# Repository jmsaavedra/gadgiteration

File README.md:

gadgiteration
=============

Hardware and firmware for the gadgiteration noisemaker v2.0

http://gadgiteration.org

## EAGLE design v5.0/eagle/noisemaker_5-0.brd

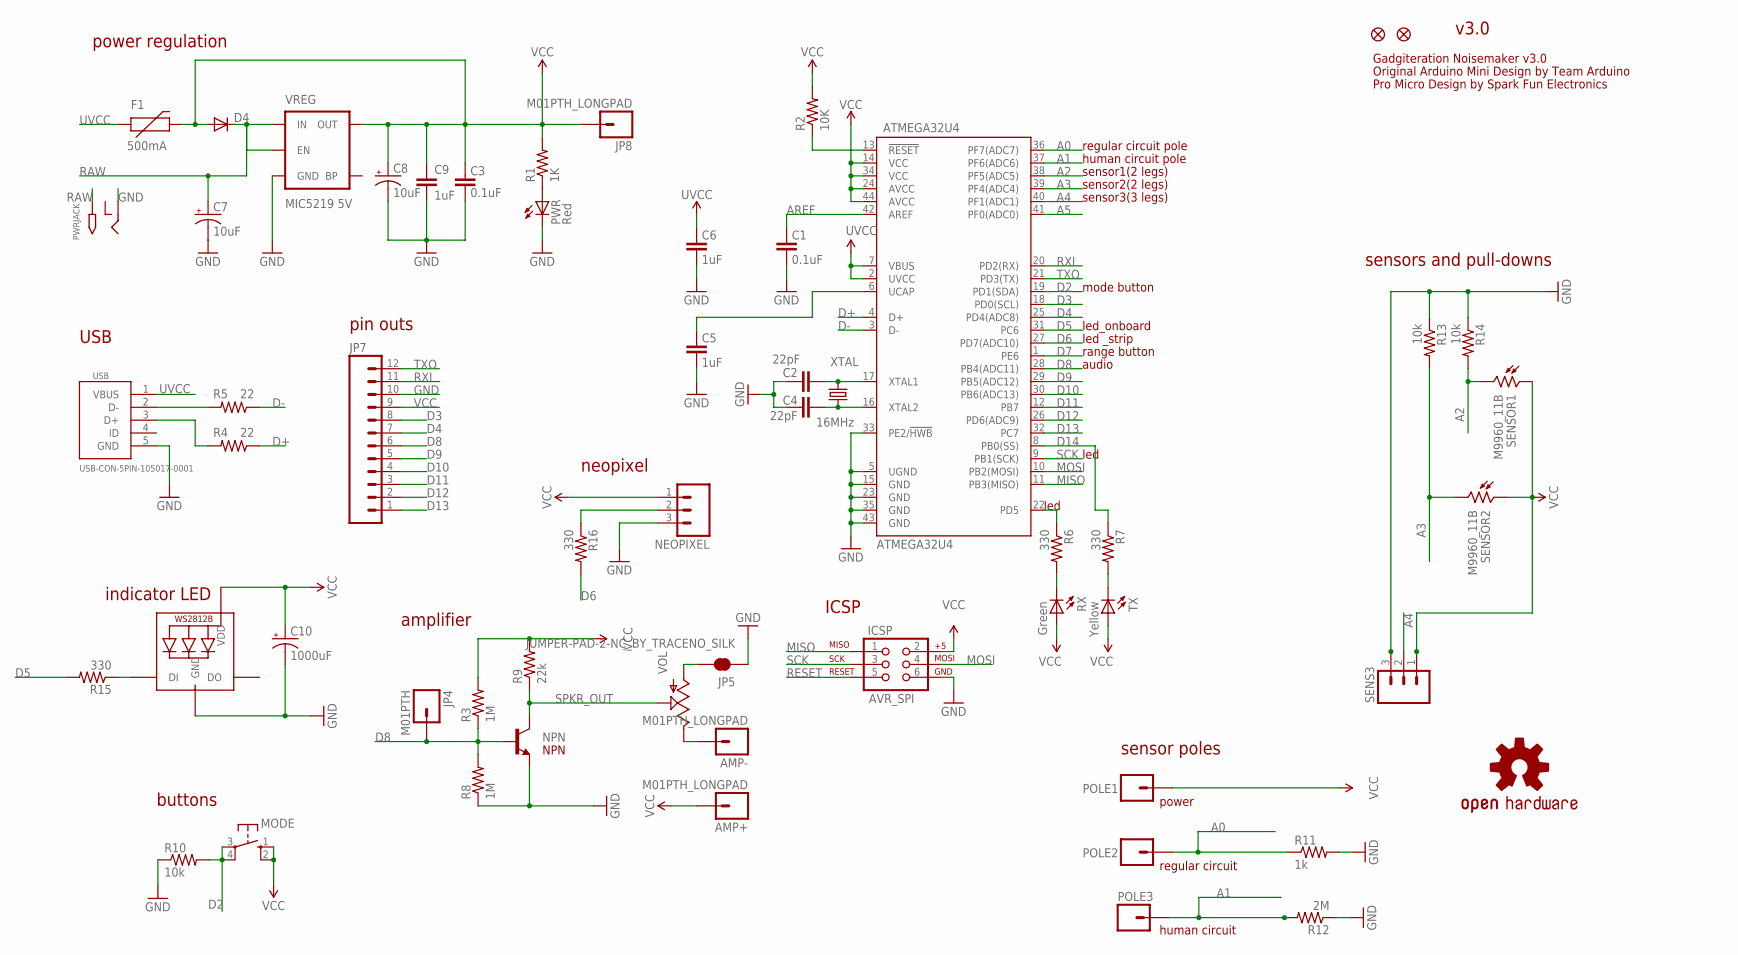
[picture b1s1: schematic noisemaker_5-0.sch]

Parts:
AMP+: M01PTH_LONGPAD; 1X01_LONGPAD
AMP-: M01PTH_LONGPAD; 1X01_LONGPAD
ATMEGA32U4: ATMEGA32U4; SPARKFUN-DIGITALIC_TQFP44
C1, C3: 0.1uF; 1206
C2, C4: 22pF; 0603-CAP
C5, C6, C9: 1uF; 1206
C7, C8: 10uF; EIA3528-KIT
C10: 1000uF; EIA3528-KIT
D4: DIODESOD; SOD-323
F1: 500mA; PTC-1206
ICSP: AVR_SPI; 2X3
JP1, JP2: FIDUCIALUFIDUCIAL; MICRO-FIDUCIAL
JP4: M01PTH; 1X01
JP5: JUMPER-PAD-2-NC_BY_TRACENO_SILK; PAD-JUMPER-2-NC_BY_TRACE_NO_SILK
JP7: M12PTH; 1X12
JP8: M01PTH_LONGPAD; 1X01_LONGPAD
LED1: WS2812B3535; LED3535
LOGO1: OSHW-LOGOM; OSHW-LOGO-M
MODE: 10-XX; B3F-10XX
NEOPIXEL: M03LONGPADS; 1X03_LONGPADS
NPN: TRANSISTOR_NPNSOT23-3; SOT23-3
POLE1, POLE2: M01ALLIGATOR-3MM; 1X01_ALLIGATOR_3MM
POLE3: M01PTH_LONGPAD; 1X01_LONGPAD
PWR: Red; CHIPLED_1206
PWRJACK: 2.1MMJACKTHM; PJ-102A
R1: 1K; 1206
R2: 10K; 1206
R3, R8: 1M; 1206
R4, R5: 22; 1206
R6, R7, R15, R16: 330; 1206
R9: 22k; 1206
R10, R13, R14: 10k; 1206
R11: 1k; 1206
R12: 2M; 1206
RX: Green; CHIPLED_1206
SENS3: M03POGO_PIN_HOLES_ONLY; 1X03_PP_HOLES_ONLY
SENSOR1, SENSOR2: M9960_11B; M9960
TX: Yellow; CHIPLED_1206
USB: USB-CON-5PIN-105017-0001; USB-MICRO-MOLEX-105017-0001
VOL: POT; ALPS_POT
VREG: MIC5219 5V; SOT23-5
XTAL: 16MHz; CRYSTAL-SMD-5X3

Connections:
A0: ATMEGA32U4.36 (PF7(ADC7)), POLE2.1@0, POLE2.1@2, R11.1
A1: ATMEGA32U4.37 (PF6(ADC6)), POLE3.1, R12.2
A2: ATMEGA32U4.38 (PF5(ADC5)), R14.2, SENSOR1.2
A3: ATMEGA32U4.39 (PF4(ADC4)), R13.2, SENSOR2.2
A4: ATMEGA32U4.40 (PF1(ADC1)), SENS3.2
A5: ATMEGA32U4.41 (PF0(ADC0))
AREF: ATMEGA32U4.42 (AREF), C1.2
D2: ATMEGA32U4.19 (PD1(SDA)), MODE.3, MODE.4 (P1), R10.2
D3: ATMEGA32U4.18 (PD0(SCL)), JP7.8
D4: ATMEGA32U4.25 (PD4(ADC8)), JP7.7
D5: ATMEGA32U4.31 (PC6), R15.2
D6: ATMEGA32U4.27 (PD7(ADC10)), R16.2
D7: ATMEGA32U4.1 (PE6)
D8: ATMEGA32U4.28 (PB4(ADC11)), JP4.1, JP7.6, NPN.1 (B), R3.1, R8.2
D9: ATMEGA32U4.29 (PB5(ADC12)), JP7.5
D10: ATMEGA32U4.30 (PB6(ADC13)), JP7.4
D11: ATMEGA32U4.12 (PB7), JP7.3
D12: ATMEGA32U4.26 (PD6(ADC9)), JP7.2
D13: ATMEGA32U4.32 (PC7), JP7.1
D14: ATMEGA32U4.8 (PB0(SS)), R7.1
D+: ATMEGA32U4.4 (D+), R4.1
D-: ATMEGA32U4.3 (D-), R5.1
GND: ATMEGA32U4.5 (UGND), ATMEGA32U4.15 (GND), ATMEGA32U4.23 (GND), ATMEGA32U4.33 (PE2/!HWB), ATMEGA32U4.35 (GND), ATMEGA32U4.43 (GND), C1.1, C2.2, C3.1, C4.2, C5.1, C6.1, C7.C (-), C8.C (-), C9.2, C10.C (-), ICSP.6, JP5.1, JP7.10, LED1.4 (GND), NEOPIXEL.3, NPN.2 (E), PWR.C, PWRJACK.RING, R8.1, R10.1, R11.2, R12.1, R13.1, R14.1, SENS3.3, USB.5 (GND), VREG.2 (GND)
MISO: ATMEGA32U4.11 (PB3(MISO)), ICSP.1
MOSI: ATMEGA32U4.10 (PB2(MOSI)), ICSP.4
unnamed: ATMEGA32U4.16 (XTAL2), C4.1, XTAL.1
unnamed: ATMEGA32U4.17 (XTAL1), C2.1, XTAL.3 (2)
unnamed: AMP-.1, VOL.P$1 (E)
unnamed: ATMEGA32U4.6 (UCAP), C5.2
unnamed: R7.2, TX.C
unnamed: JP5.2, VOL.P$3 (A)
unnamed: R6.2, RX.C
unnamed: LED1.1 (DI), R15.1
unnamed: NEOPIXEL.2, R16.1
unnamed: PWR.A, R1.1
unnamed: R4.2, USB.3 (D+)
unnamed: R5.2, USB.2 (D-)
RAW: C7.A (+), D4.1 (C), PWRJACK.TIP, VREG.1 (IN), VREG.3 (EN)
RESET: ATMEGA32U4.13 (!RESET), ICSP.5, R2.1
RXI: ATMEGA32U4.20 (PD2(RX)), JP7.11
SCK: ATMEGA32U4.9 (PB1(SCK)), ICSP.3
SPKR_OUT: NPN.3 (C), R9.1, VOL.P$2 (S)
TXLED: ATMEGA32U4.22 (PD5), R6.1
TXO: ATMEGA32U4.21 (PD3(TX)), JP7.12
UVCC: ATMEGA32U4.2 (UVCC), ATMEGA32U4.7 (VBUS), C6.2, F1.1, USB.1 (VBUS)
VCC: AMP+.1, ATMEGA32U4.14 (VCC), ATMEGA32U4.24 (AVCC), ATMEGA32U4.34 (VCC), ATMEGA32U4.44 (AVCC), C3.2, C8.A (+), C9.1, C10.A (+), D4.2 (A), F1.2, ICSP.2, JP7.9, JP8.1, LED1.2 (VDD), MODE.1 (S), MODE.2 (S1), NEOPIXEL.1, POLE1.1@0, POLE1.1@2, R1.2, R2.2, R3.2, R9.2, RX.A, SENS3.1, SENSOR1.1, SENSOR2.1, TX.A, VREG.5 (OUT)

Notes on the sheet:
Original Arduino Mini Design by Team Arduino
Pro Micro Design by Spark Fun Electronics
v3.0
power regulation
pin outs
USB
NPN
amplifier
sensors and pull-downs
ICSP
buttons
sensor poles
human circuit
regular circuit
power
Gadgiteration Noisemaker v3.0
sensor3(3 legs)
sensor1(2 legs)
sensor2(2 legs)
human circuit pole
regular circuit pole
mode button
range button
audio
led_onboard
led
led _strip
neopixel
indicator LED

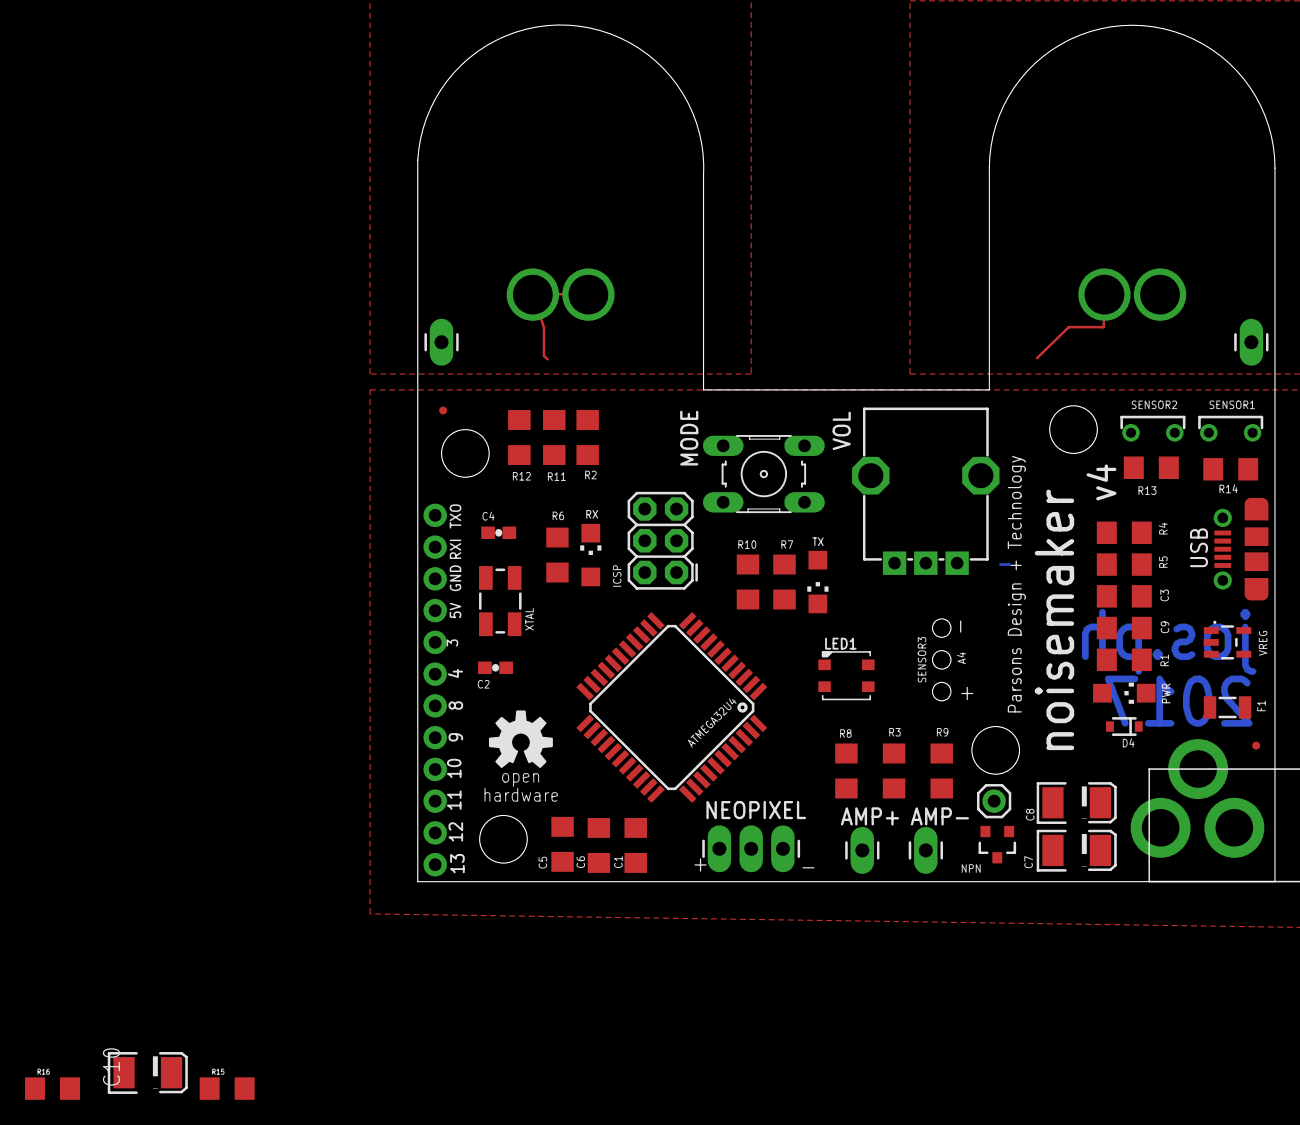
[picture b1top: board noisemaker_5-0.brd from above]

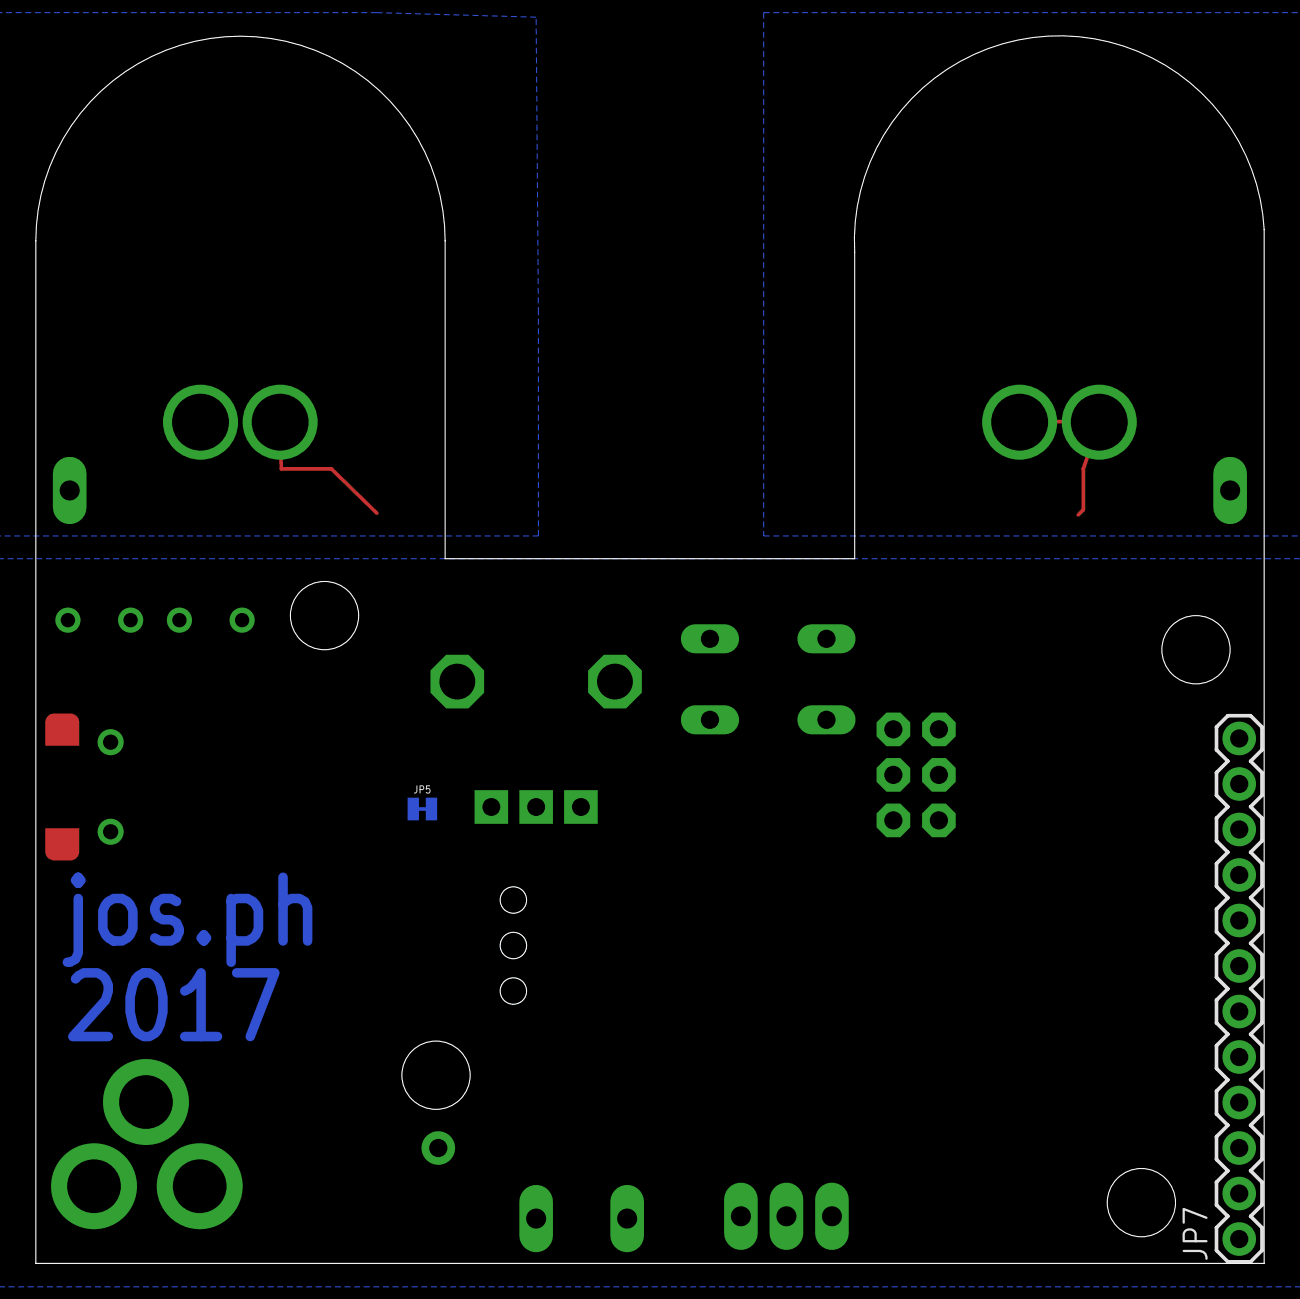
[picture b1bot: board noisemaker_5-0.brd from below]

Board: 2 copper layers, 68.6 x 68.5 mm, 57 parts (2 on the bottom side), 44 nets.

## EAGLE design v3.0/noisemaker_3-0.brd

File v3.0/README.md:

gadgIteration hardware v3.0
=============

ATmega32u4 Implementation of the Noisemaker!

###digital pinouts###

* D2 - Mode Button
* D5 - on-board LEDs. HIGH/LOW to flip LED1/LED2
* D6 - Neopixel Connection
* D7 - Range Button
* D8 - Audio out. NPN amplifier to speaker.

###analog pinouts###

* A0 - Standard Alligator In
* A1 - Human Circuit In
* A2 - SENSOR 1. 10k pull-down.
* A3 - SENSOR 2. 10k pull-down.
* A4 - SENSOR 3. VCC - SENS - GND.

###known bugs###

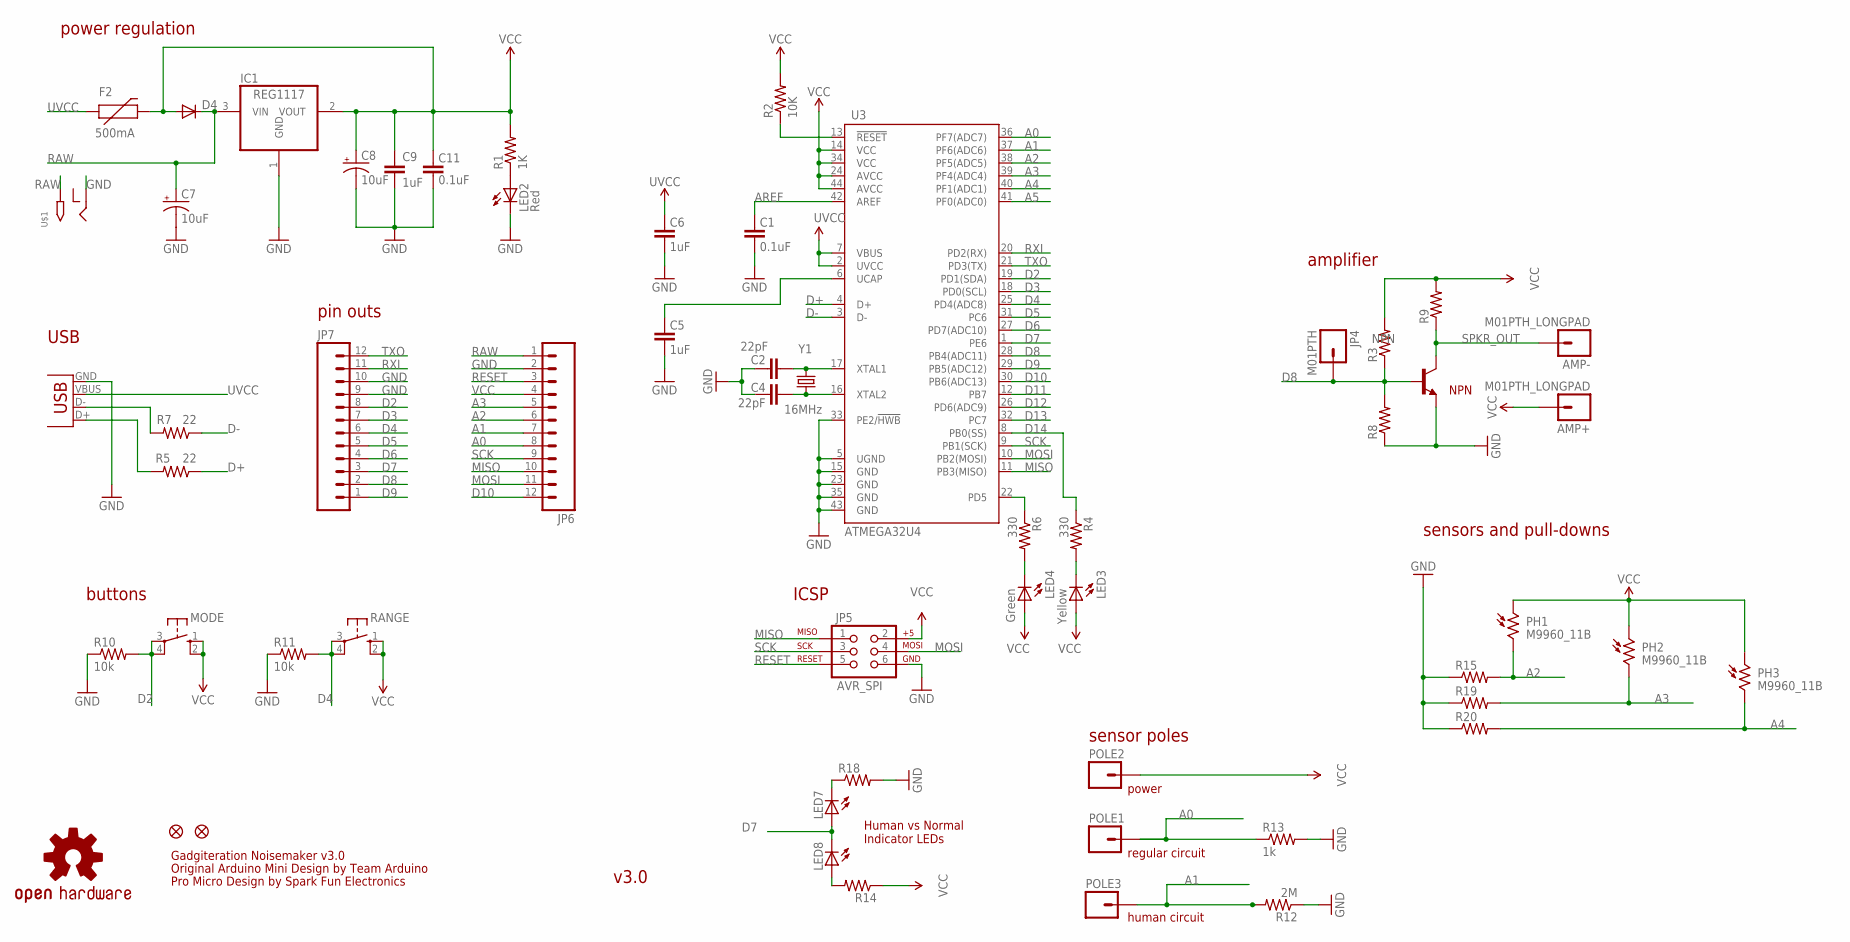
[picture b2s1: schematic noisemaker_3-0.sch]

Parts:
AMP+: M01PTH_LONGPAD; 1X01_LONGPAD
AMP-: M01PTH_LONGPAD; 1X01_LONGPAD
C1, C11: 0.1uF; 1206
C2, C4: 22pF; 0603-CAP
C5, C6, C9: 1uF; 1206
C7, C8: 10uF; EIA3528-KIT
D4: DIODESOD; SOD-323
F2: 500mA; PTC-1206
IC1: REG1117; SOT223
JP1, JP2: FIDUCIALUFIDUCIAL; MICRO-FIDUCIAL
JP3: USB-B; USB-B-PTH
JP4: M01PTH; 1X01
JP5: AVR_SPI; 2X3
JP6, JP7: M12PTH; 1X12
LED2: Red; CHIPLED_1206
LED3: Yellow; CHIPLED_1206
LED4: Green; CHIPLED_1206
LED7, LED8: LED3MM
MODE: 10-XX; B3F-10XX
NPN: -NPN-TO220V; TO220V
PH1, PH2, PH3: M9960_11B; M9960
POLE1, POLE2, POLE3: M01PTH_LONGPAD; 1X01_LONGPAD
R1: 1K; 1206
R2: 10K; 1206
R3, R8, R9, R14, R15, R18, R19, R20: RESISTOR1206; 1206
R4, R6: 330; 1206
R5, R7: 22; 1206
R10, R11: 10k; 1206
R12: 2M; 1206
R13: 1k; 1206
RANGE: 10-XX; B3F-10XX
U3: ATMEGA32U4; SPARKFUN-DIGITALIC_TQFP44
U$1: 2.1MMJACKTHM; PJ-102A
U$3: OSHW-LOGOS; OSHW-LOGO-S
Y1: 16MHz; CRYSTAL-SMD-5X3

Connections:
A0: JP6.8, POLE1.1, R13.1, U3.36 (PF7(ADC7))
A1: JP6.7, POLE3.1, R12.2, U3.37 (PF6(ADC6))
A2: JP6.6, PH1.2, R15.2, U3.38 (PF5(ADC5))
A3: JP6.5, PH2.2, R19.2, U3.39 (PF4(ADC4))
A4: PH3.2, R20.2, U3.40 (PF1(ADC1))
A5: U3.41 (PF0(ADC0))
AREF: C1.2, U3.42 (AREF)
D2: JP7.8, MODE.3, MODE.4 (P1), R10.2, U3.19 (PD1(SDA))
D3: JP7.7, U3.18 (PD0(SCL))
D4: JP7.6, R11.2, RANGE.3, RANGE.4 (P1), U3.25 (PD4(ADC8))
D5: JP7.5, U3.31 (PC6)
D6: JP7.4, U3.27 (PD7(ADC10))
D7: JP7.3, LED7.A, LED8.K (C), U3.1 (PE6)
D8: JP4.1, JP7.2, NPN.1 (B), R3.1, R8.2, U3.28 (PB4(ADC11))
D9: JP7.1, U3.29 (PB5(ADC12))
D10: JP6.12, U3.30 (PB6(ADC13))
D11: U3.12 (PB7)
D12: U3.26 (PD6(ADC9))
D13: U3.32 (PC7)
D14: R4.1, U3.8 (PB0(SS))
D+: R5.1, U3.4 (D+)
D-: R7.1, U3.3 (D-)
GND: C1.1, C2.2, C4.2, C5.1, C6.1, C7.C (-), C8.C (-), C9.2, C11.1, IC1.1 (GND), JP3.GND, JP5.6, JP6.2, JP7.9, JP7.10, LED2.C, NPN.3 (E), R8.1, R10.1, R11.1, R12.1, R13.2, R15.1, R18.2, R19.1, R20.1, U3.5 (UGND), U3.15 (GND), U3.23 (GND), U3.33 (PE2/!HWB), U3.35 (GND), U3.43 (GND), U$1.RING
MISO: JP5.1, JP6.10, U3.11 (PB3(MISO))
MOSI: JP5.4, JP6.11, U3.10 (PB2(MOSI))
unnamed: C4.1, U3.16 (XTAL2), Y1.1
unnamed: C2.1, U3.17 (XTAL1), Y1.3 (2)
unnamed: C5.2, U3.6 (UCAP)
unnamed: LED3.C, R4.2
unnamed: LED4.C, R6.2
unnamed: JP3.D+, R5.2
unnamed: JP3.D-, R7.2
unnamed: LED2.A, R1.1
unnamed: LED7.K (C), R18.1
unnamed: LED8.A, R14.2
RAW: C7.A (+), D4.1 (C), IC1.3 (VIN), JP6.1, U$1.TIP
RESET: JP5.5, JP6.3, R2.1, U3.13 (!RESET)
RXI: JP7.11, U3.20 (PD2(RX))
SCK: JP5.3, JP6.9, U3.9 (PB1(SCK))
SPKR_OUT: AMP-.1, NPN.2 (C), R9.1
TXLED: R6.1, U3.22 (PD5)
TXO: JP7.12, U3.21 (PD3(TX))
UVCC: C6.2, F2.1, JP3.VBUS, U3.2 (UVCC), U3.7 (VBUS)
VCC: AMP+.1, C8.A (+), C9.1, C11.2, D4.2 (A), F2.2, IC1.2 (VOUT), JP5.2, JP6.4, LED3.A, LED4.A, MODE.1 (S), MODE.2 (S1), PH1.1, PH2.1, PH3.1, POLE2.1, R1.2, R2.2, R3.2, R9.2, R14.1, RANGE.1 (S), RANGE.2 (S1), U3.14 (VCC), U3.24 (AVCC), U3.34 (VCC), U3.44 (AVCC)

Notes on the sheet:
Original Arduino Mini Design by Team Arduino
Pro Micro Design by Spark Fun Electronics
v3.0
power regulation
pin outs
USB
NPN
amplifier
sensors and pull-downs
ICSP
Human vs Normal Indicator LEDs
buttons
sensor poles
human circuit
regular circuit
power
Gadgiteration Noisemaker v3.0

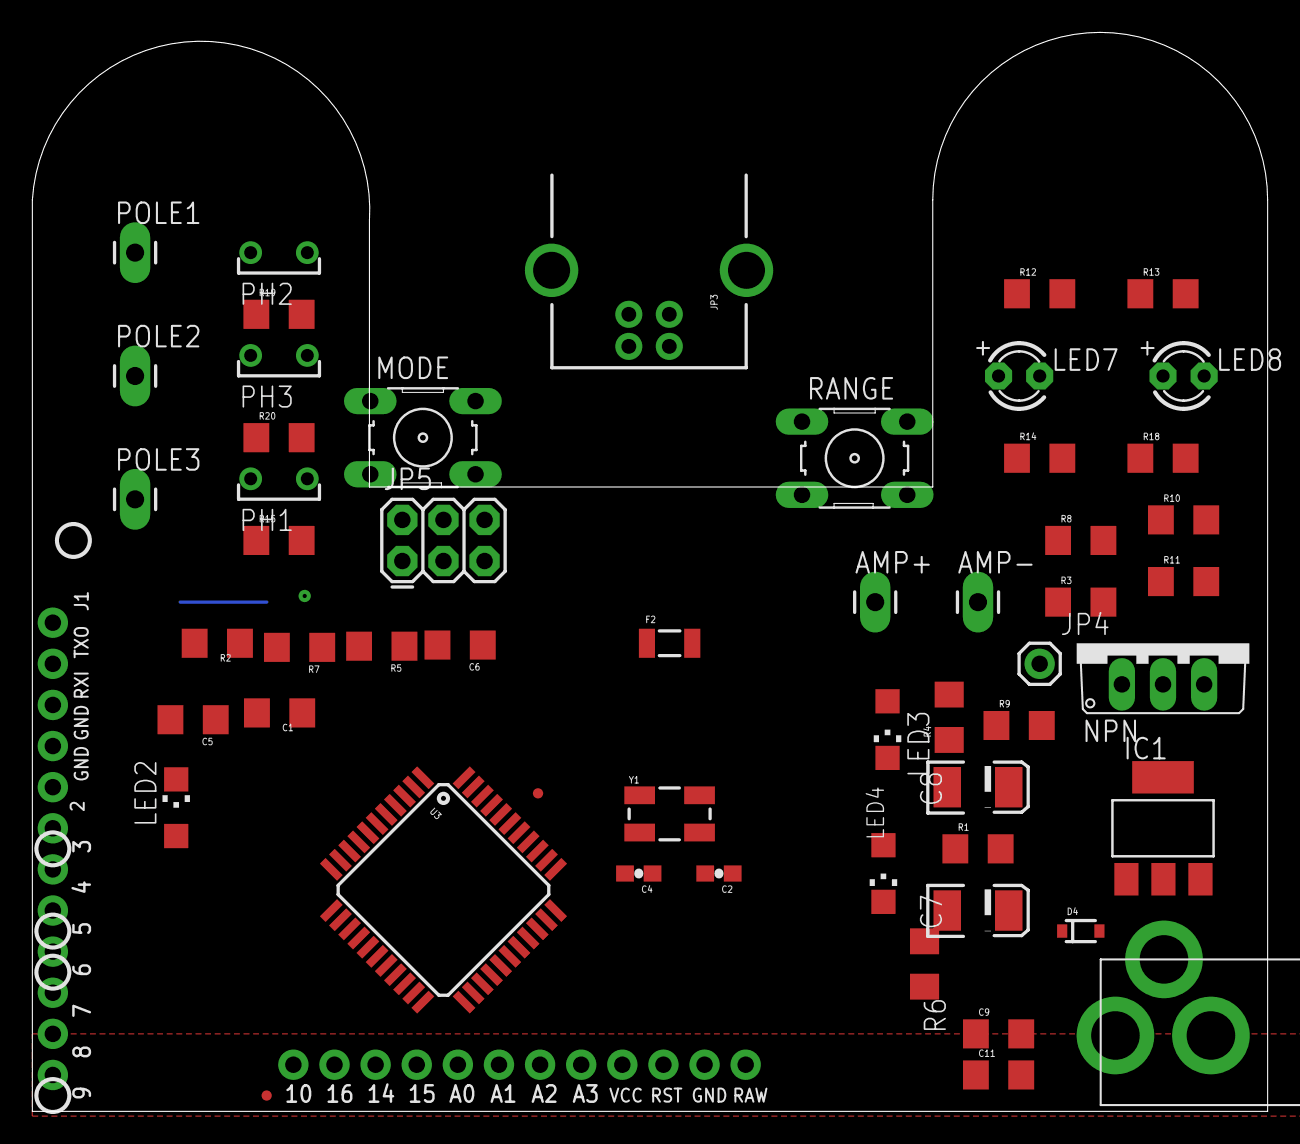
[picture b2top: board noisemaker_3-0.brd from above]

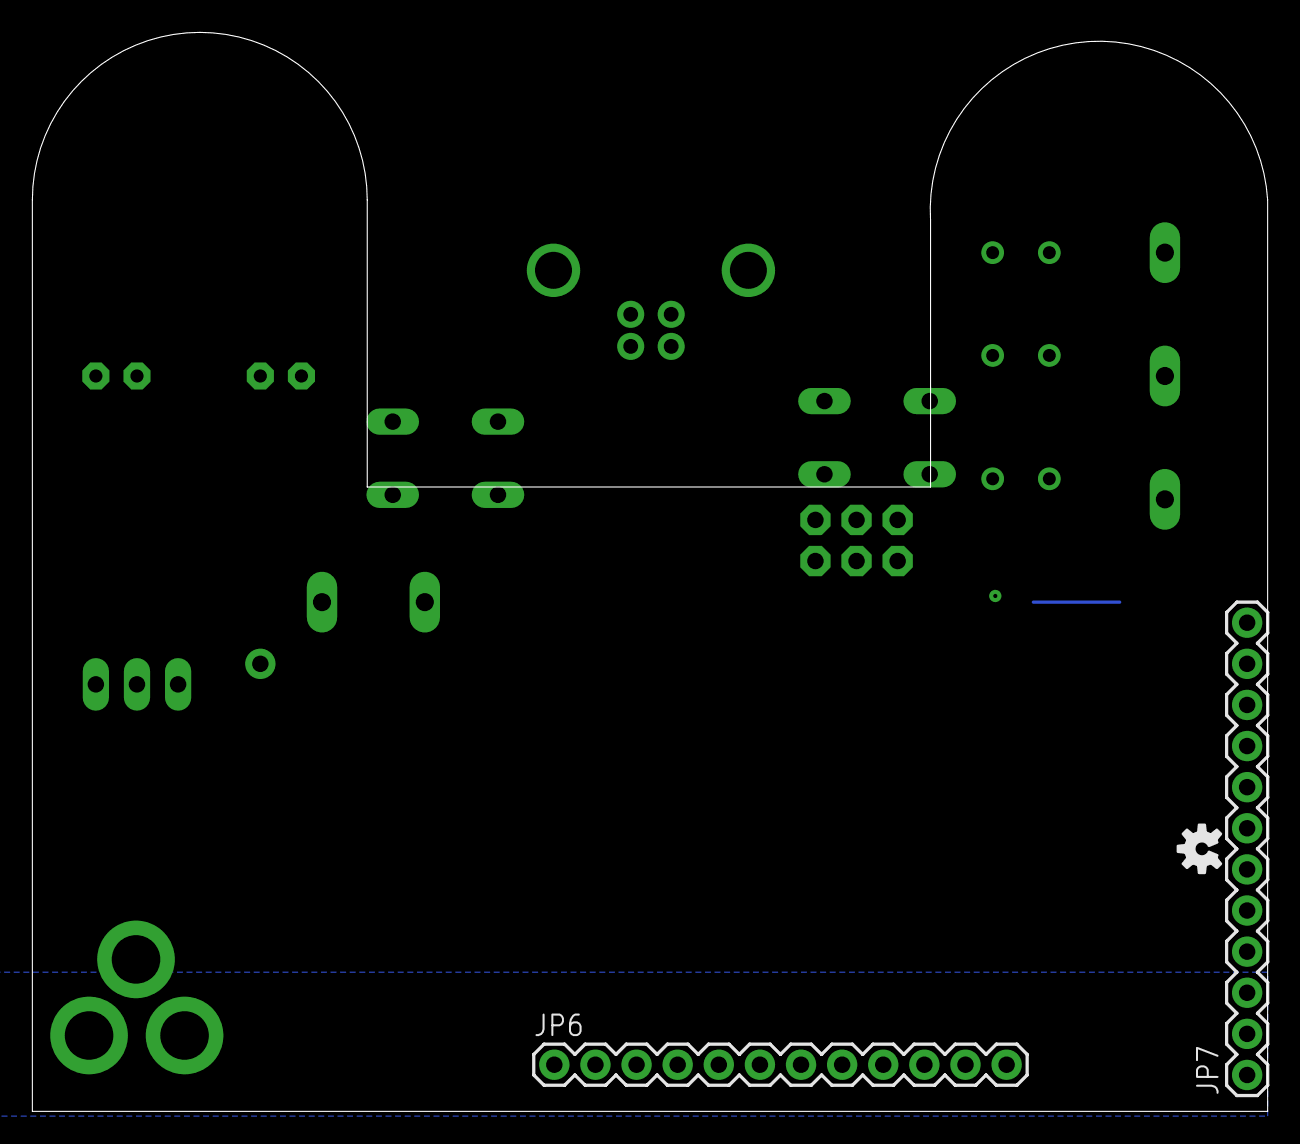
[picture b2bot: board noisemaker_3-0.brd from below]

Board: 2 copper layers, 76.3 x 66.7 mm, 57 parts (3 on the bottom side), 40 nets.

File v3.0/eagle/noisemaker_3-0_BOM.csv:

board ID,Qty,Value,Device,Package,Parts,Atmel 44-pin 8-bit Microcontroller ,link,MF,MPN
ATMEGA32U4,1,ATMEGA32U4,ATMEGA32U4TQFP,SPARKFUN-DIGITALIC_TQFP44,ATMEGA32U4,Atmel 44-pin 8-bit Microcontroller,https://www.sparkfun.com/products/11181,,
D4,1,,DIODESOD,SOD-323,D4,Diode,http://www.mouser.com/ProductDetail/Vishay-Semiconductors/BA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,,
NPN,1,DNP,DO NOT POPULATE,SOT23-3,NPN,DO NOT POPULATE,,,
"C2, C4",2,18pF,CAP0603-CAP,0603-CAP,C2,C4,http://www.mouser.com/ProductDetail/Vishay-Vitramon/VJ0603A2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,Capacitor,
"C1, C11",2,0.1uF,CAP1206,1206,C1,C11,http://www.mouser.com/ProductDetail/Vishay-Vitramon/VJ1206Y1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,Capacitor,
"C7, C8",2,10uF,CAP_POL3528-KIT,EIA3528-KIT,C7,C8,https://www.mouser.com/ProjectManager/ProjectDetail.aspx?Sta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,Capacitor Polarized,
"C5, C6, C9",3,1uF,CAP1206,1206,C5,C6,https://www.mouser.com/Search/ProductDetail.aspx?R=VJ1206V10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,C9,Capacitor
"R1, R13",2,1K,RESISTOR1206,1206,R1,R13,https://www.mouser.com/Search/ProductDetail.aspx?R=RK73B2BTT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,,
"R2, R10, R11, R15, R19",5,10k,RESISTOR1206,1206,R10,R11,https://www.mouser.com/Search/ProductDetail.aspx?R=CRCW12061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,R15,R19
"R3, R8",2,1M,RESISTOR1206,1206,R3,R8,https://www.mouser.com/Search/ProductDetail.aspx?R=RV1206FR-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,Resistor,
"R5, R7",2,22,RESISTOR1206,1206,R5,R7,https://www.mouser.com/Search/ProductDetail.aspx?R=CRCW12062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,Resistor,
R9,1,22k,RESISTOR1206,1206,R9,Resistor,https://www.mouser.com/Search/ProductDetail.aspx?R=CRCW12062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,,
R12,1,2M,RESISTOR1206,1206,R12,Resistor,https://www.mouser.com/Search/ProductDetail.aspx?R=RV1206FR-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,,
"R4, R6, R14, R18",4,330,RESISTOR1206,1206,R4,R6,https://www.mouser.com/Search/ProductDetail.aspx?R=CRCW12063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,R14,R18
F2,1,500mA,PTCSMD,PTC-1206,F2,Resettable Fuse PTC,https://www.mouser.com/Search/ProductDetail.aspx?R=PTS120624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,,
IC1,1,REG1117,REG1117,SOT223,IC1,800mA and 1A Low Dropout (LDO) Positive Regulator,https://www.mouser.com/Search/ProductDetail.aspx?R=AZ1117H-5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,,REG1117
XTAL,1,16MHz,CRYSTAL5X3,CRYSTAL-SMD-5X3,XTAL,Crystals,https://www.mouser.com/Search/ProductDetail.aspx?R=ABM3C-16.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,,
USB,1,USB-B,USBPTH,USB-B-PTH,JP3,USB Connectors,https://www.mouser.com/Search/ProductDetail.aspx?R=154-2442-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,,
RX,1,Blue,LEDCHIPLED_1206,CHIPLED_1206,TX,LED,https://www.mouser.com/Search/ProductDetail.aspx?R=LTST-C150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,,
PWR,1,Red,LEDCHIPLED_1206,CHIPLED_1206,PWR,LED,http://www.mouser.com/Search/ProductDetail.aspx?R=LH_N974-KN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,,
TX,1,Green,LEDCHIPLED_1206,CHIPLED_1206,RX,LED,http://www.mouser.com/ProductDetail/OSRAM-Opto-Semiconductor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,,
,2,,LED3MM,LED3MM,LED1,LED2,https://www.mouser.com/Search/ProductDetail.aspx?R=3GDL-201v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,LED,
,1,2.1MMJACK,2.1MMJACKTHM,PJ-102A,U$1,2.1mm x 5.5mm THM DC jack,https://www.mouser.com/Search/ProductDetail.aspx?R=163-179PH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,4UCON part #05537,
,2,,10-XX,B3F-10XX,MODE,RANGE,https://www.mouser.com/Search/ProductDetail.aspx?R=PTS645SK7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,OMRON SWITCH,

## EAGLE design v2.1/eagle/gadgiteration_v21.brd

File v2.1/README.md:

gadgIteration hardware v2.1
=============

###digital pinouts###

* D2  - Button "MODE"
* D4  - Button "RANGE"
* D6  - LED Strip
* D7  - MODE LEDs (high=right ON, low=left ON)
* D8  - speaker/audio output
* D13 - onboard green LED

###analog pinouts###

* A0 - Standard Alligator In
* A1 - Human Circuit In
* A2 - SENSOR 1
* A3 - SENSOR 2
* A4 - SENSOR 3

###known bugs, updates for v2.2 or v3.0###

* PWR switch should be implemented, if we want an external power switch on enclosure.
* RANGE button should be moved to D3, so that we can use it as an interrupt
  * [attachInterrupts](http://arduino.cc/en/Reference/attachInterrupt)

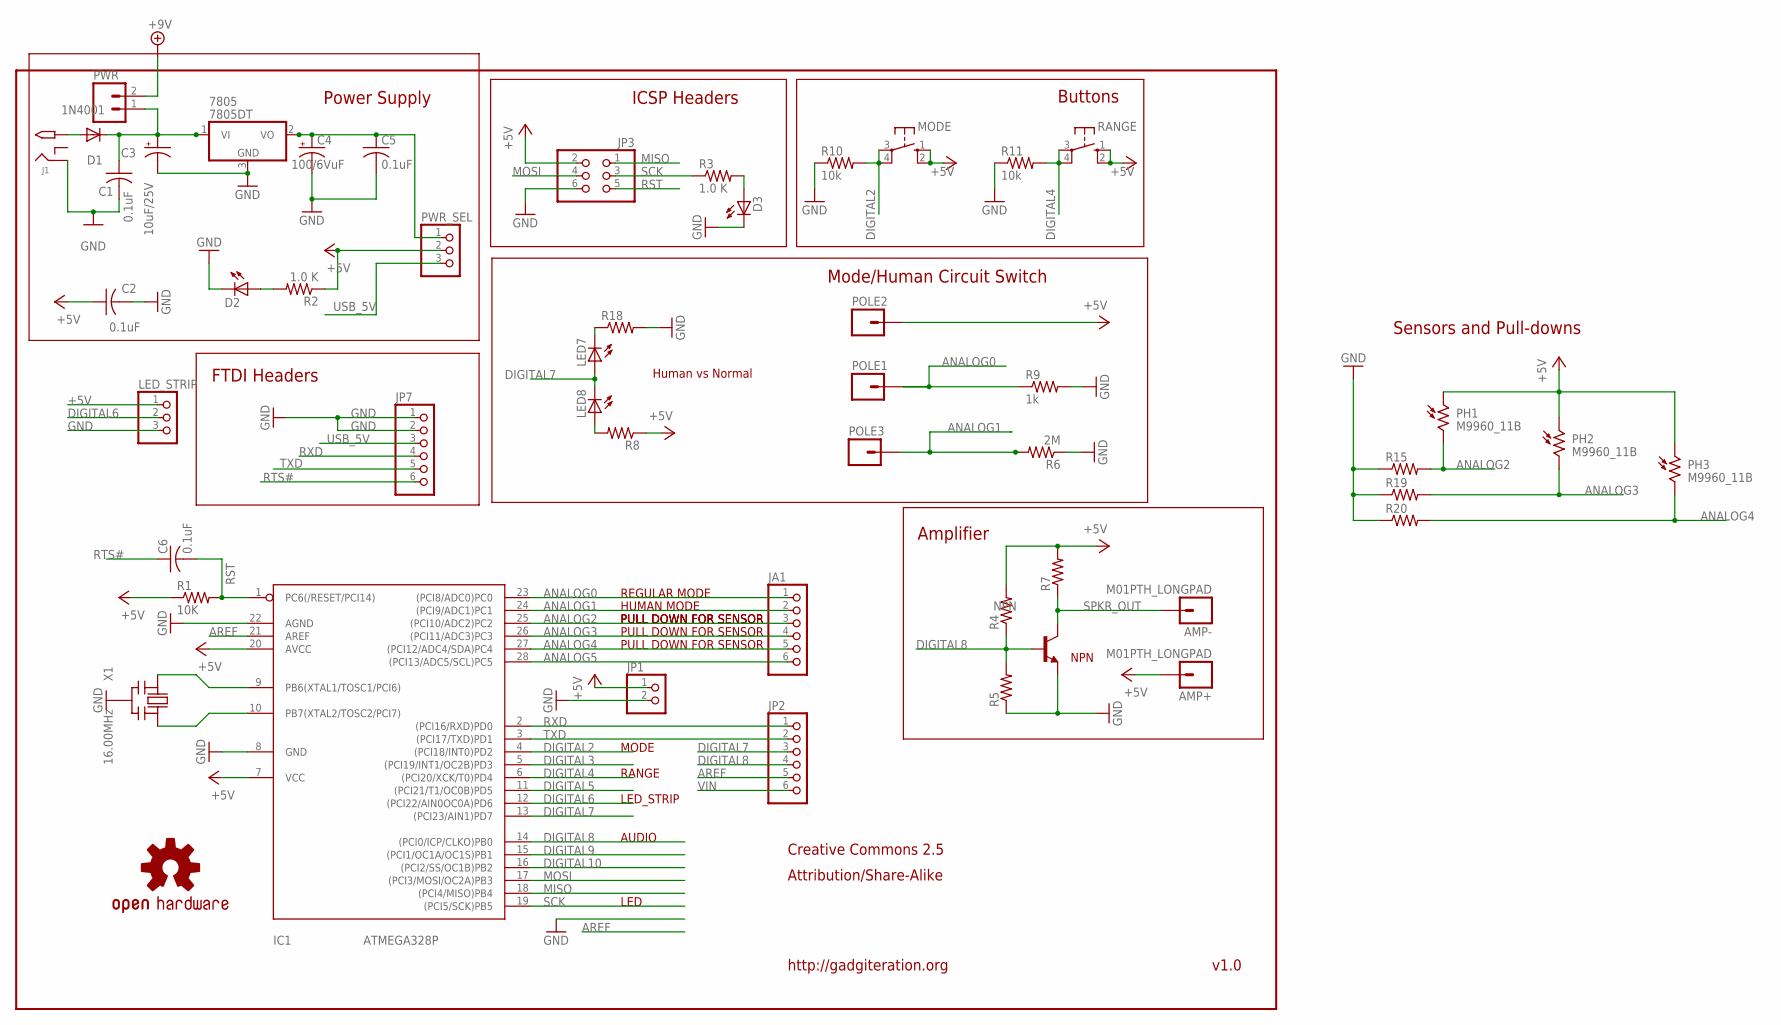
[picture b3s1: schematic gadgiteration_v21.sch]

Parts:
7805: 7805DT; TO252
AMP+: M01PTH_LONGPAD; 1X01_LONGPAD
AMP-: M01PTH_LONGPAD; 1X01_LONGPAD
C1, C2, C5, C6: 0.1uF; C025-025X050
C3: 10uF/25V; E2,5-6
C4: 100/6VuF; E2,5-6
D1: 1N4001; DIODE-1N4001
D2: LED3MM
D3: Green; LED3MM
IC1: ATMEGA328P; DIL28/3
J1: 2.1MMJACK; PJ-102A
JA1: PINHD-1X6CB; 1X06-CLEANBIG
JP1: PINHD-1X2CB; 1X02-CB
JP2: PINHD-1X6CB; 1X06-CLEANBIG
JP3: PINHD-2X3; 2X03
JP7: PINHD-1X6CLEAN; 1X06-CLEAN
LED7, LED8: LED3MM
LED_STRIP: PINHD-1X3; 1X03
LOGO1: OSHW-LOGOM; OSHW-LOGO-M
MODE: 10-XX; B3F-10XX
NPN: -NPN-TO220V; TO220V
PH1, PH2, PH3: M9960_11B; M9960
POLE1, POLE2, POLE3: M01PTH_LONGPAD; 1X01_LONGPAD
PWR: M02LOCK; 1X02_LOCK
PWR_SEL: PINHD-1X3; 1X03
R1: 10K; 0204/5
R2, R3: 1.0 K; 0204/5
R4, R5, R7, R8, R15, R18, R19, R20: R-US_0204/5; 0204/5
R6: 2M; 0204/5
R9: 1k; 0204/5
R10, R11: 10k; 0204/5
RANGE: 10-XX; B3F-10XX
X1: 16.00MHz; CERM_OSC

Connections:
+5V: AMP+.1, C2.1, IC1.7 (VCC), IC1.20 (AVCC), JP1.1, JP3.2, LED_STRIP.1, MODE.1 (S), MODE.2 (S1), PH1.1, PH2.1, PH3.1, POLE2.1, PWR_SEL.2, R1.1, R2.1, R4.2, R7.2, R8.1, RANGE.1 (S), RANGE.2 (S1)
+9V: PWR.2
ANALOG0: IC1.23 ((PCI8/ADC0)PC0), JA1.1, POLE1.1, R9.1
ANALOG1: IC1.24 ((PCI9/ADC1)PC1), JA1.2, POLE3.1, R6.2
ANALOG2: IC1.25 ((PCI10/ADC2)PC2), JA1.3, PH1.2, R15.2
ANALOG3: IC1.26 ((PCI11/ADC3)PC3), JA1.4, PH2.2, R19.2
ANALOG4: IC1.27 ((PCI12/ADC4/SDA)PC4), JA1.5, PH3.2, R20.2
ANALOG5: IC1.28 ((PCI13/ADC5/SCL)PC5), JA1.6
AREF: IC1.21 (AREF), JP2.5
DIGITAL2: IC1.4 ((PCI18/INT0)PD2), MODE.3, MODE.4 (P1), R10.2
DIGITAL3: IC1.5 ((PCI19/INT1/OC2B)PD3)
DIGITAL4: IC1.6 ((PCI20/XCK/T0)PD4), R11.2, RANGE.3, RANGE.4 (P1)
DIGITAL5: IC1.11 ((PCI21/T1/OC0B)PD5)
DIGITAL6: IC1.12 ((PCI22/AIN0OC0A)PD6), LED_STRIP.2
DIGITAL7: IC1.13 ((PCI23/AIN1)PD7), JP2.3, LED7.A, LED8.K (C)
DIGITAL8: IC1.14 ((PCI0/ICP/CLKO)PB0), JP2.4, NPN.1 (B), R4.1, R5.2
DIGITAL9: IC1.15 ((PCI1/OC1A/OC1S)PB1)
DIGITAL10: IC1.16 ((PCI2/SS/OC1B)PB2)
GND: 7805.3 (GND), C1.2, C2.2, C3.-, C4.-, C5.2, D2.K (C), D3.K (C), IC1.8 (GND), IC1.22 (AGND), J1.RING, JP1.2, JP3.6, JP7.1, JP7.2, LED_STRIP.3, NPN.3 (E), R5.1, R6.1, R9.2, R10.1, R11.1, R15.1, R18.2, R19.1, R20.1, X1.P$2 (GND)
MISO: IC1.18 ((PCI4/MISO)PB4), JP3.1
MOSI: IC1.17 ((PCI3/MOSI/OC2A)PB3), JP3.4
unnamed: IC1.9 (PB6(XTAL1/TOSC1/PCI6)), X1.P$1 (IN)
unnamed: IC1.10 (PB7(XTAL2/TOSC2/PCI7)), X1.P$3 (OUT)
unnamed: D2.A, R2.2
unnamed: D3.A, R3.2
unnamed: LED7.K (C), R18.1
unnamed: LED8.A, R8.2
unnamed: D1.A, J1.TIP
unnamed: 7805.2 (VO), C4.+, C5.1, PWR_SEL.1
RST: C6.2, IC1.1 (PC6(/RESET/PCI14)), JP3.5, R1.2
RTS#: C6.1, JP7.6
RXD: IC1.2 ((PCI16/RXD)PD0), JP2.1, JP7.4
SCK: IC1.19 ((PCI5/SCK)PB5), JP3.3, R3.1
SPKR_OUT: AMP-.1, NPN.2 (C), R7.1
TXD: IC1.3 ((PCI17/TXD)PD1), JP2.2, JP7.5
USB_5V: JP7.3, PWR_SEL.3
VIN: 7805.1 (VI), C1.1, C3.+, D1.C, JP2.6, PWR.1

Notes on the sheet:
Power Supply
v1.0
http://gadgiteration.org
Creative Commons 2.5
Attribution/Share-Alike
LED
AUDIO
MODE
RANGE
LED_STRIP
ICSP Headers
Buttons
Mode/Human Circuit Switch
FTDI Headers
NPN
Amplifier
Human vs Normal
REGULAR MODE
HUMAN MODE
PULL DOWN FOR SENSOR
Sensors and Pull-downs

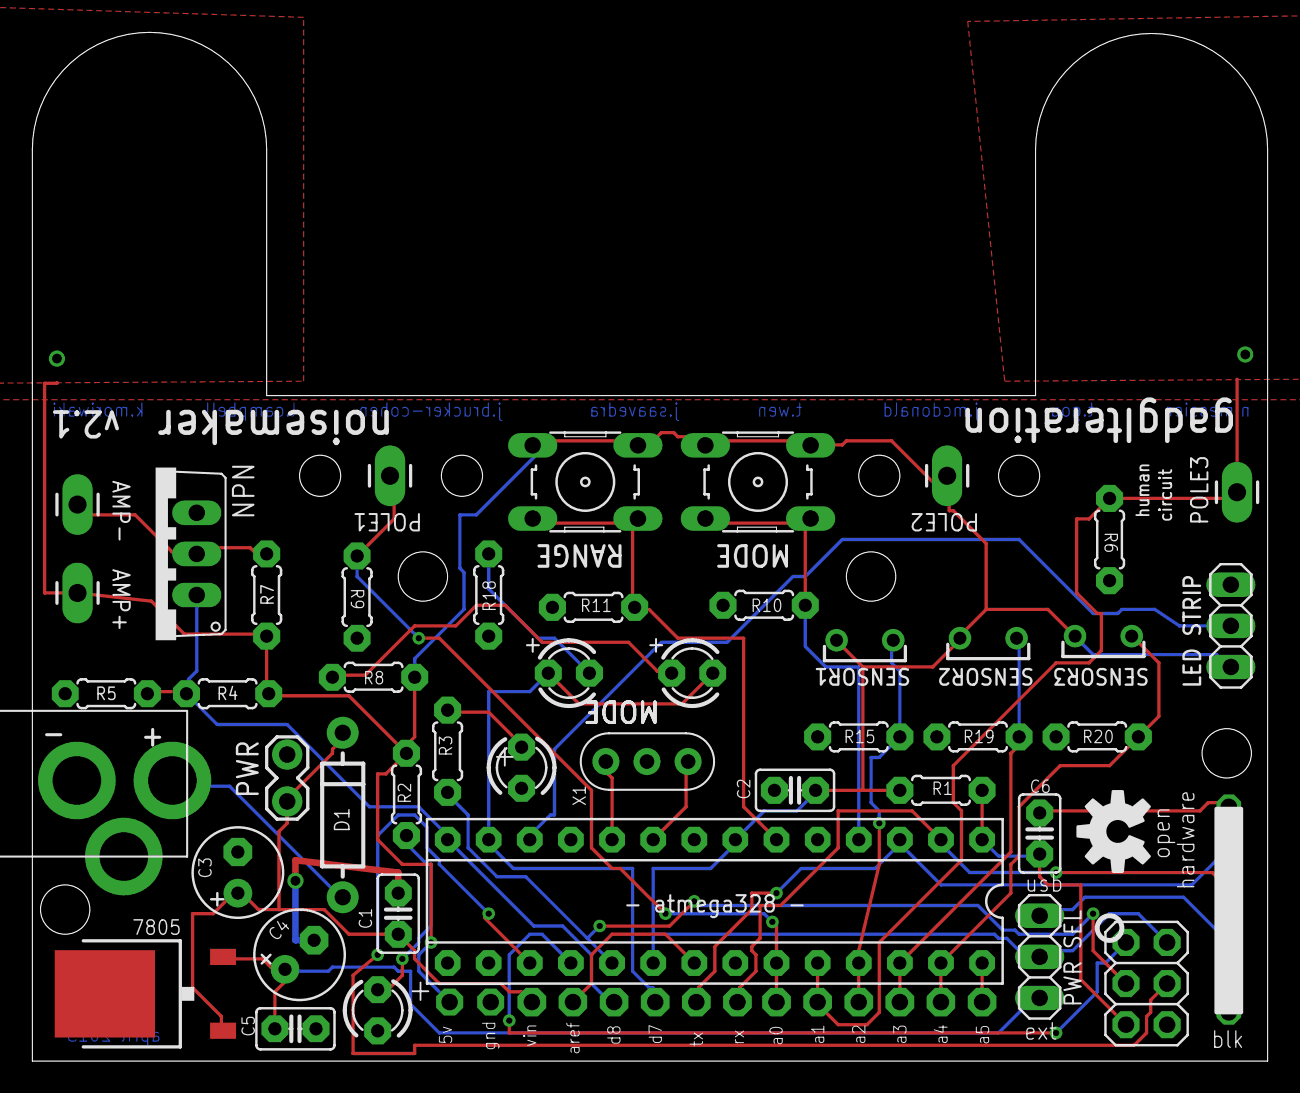
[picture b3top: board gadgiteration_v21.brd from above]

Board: 2 copper layers, 76.3 x 63.5 mm, 50 parts (0 on the bottom side), 32 nets.

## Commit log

2013-07-01 added eagle schematic and board, arduino firmware
2014-01-17 added several draft sketches
2014-02-24 added gitignore
2014-02-24 added v21 files, including readme and eagle files
2014-02-24 refactored repository folder structure
2014-02-24 added buttonTest01
2014-02-24 updated _03 LED STRIP sketch, still in progress
2014-02-24 added arduino folder to v2.1
2014-02-24 updated 2.1 readme known bugs
2014-04-10 adding bcal arduino code - havent changed the button mode
2014-04-24 code for one button
2014-05-04 updated led strip examples
2014-05-04 board 3.0
2014-05-04 updated gitignore
2014-05-04 updating with gitignore
2014-05-04 updated with gitignore implemented
2014-05-04 updated board, schematic comments
2014-05-04 updated readme, folder structure
2014-05-05 board updates...
2014-05-06 updated board layout
2014-05-06 updated board layout tues
2014-05-07 update label
2014-05-07 update files
2014-05-07 merging in @shanqiu's latest updates
2014-05-07 board file
    text has been updated, layout is completed. needs logos, names, more text love.
2014-05-08 board layout, all text complete. ready for manufacture, RC1
2014-05-08 updated minor text in board file
2014-05-08 fixed critical outline error
2014-05-08 small adjustments, this is final board
2014-05-09 adding gerber files
2014-05-09 added BOM.csv file
2014-05-27 updated BOM and PLIST files for quotes!
2014-05-28 updated voltage regulator, added second footprint for NPN options
2014-05-28 upated BOM, Partslist, and gerber files
2014-07-11 code for dorkshop
2014-10-12 updated readme with v3.0 pinouts and sketch_DC_3.0
2017-03-04 added v4 with new vreg, volume pot, new eagle v
2017-03-10 4.0 completed with gerber exports
2017-03-13 added v4 BOM
2017-06-26 added arduino sketches for v4
2017-06-26 added v5 board updates

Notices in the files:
parts and their libraries:
SparkFun-Passives: Licensing: CC v3.0 Share-Alike You are welcome to use this library for commercial purposes.
SparkFun-Electromechanical: Licensing: Creative Commons ShareAlike 4.0 International - https://creativecommons.org/licenses/by-sa/4.0
